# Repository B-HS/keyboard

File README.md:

# split-65

좌(30키)·우(35키) = **65키 분리형(split) 핫스왑 기계식 키보드 케이스**.
JSCAD(`@jscad/modeling`)로 파라메트릭 모델링하고, three.js 실시간 뷰어로 보며 설계하고, **FDM(A1 mini)용 3D STL**과 CNC/레이저컷용 **2D DXF** 두 경로로 export한다. **현재 제작 경로는 FDM 3D 프린트**(나사·인서트 외 전부 출력) — 아크릴 DXF 경로는 병행 보존.

> **monorepo (v0.0.1~).** React + TypeScript 뷰어(`src/`, FSD) 위에 프로젝트가 독립적으로 올라간다 — `65/`(split-65) · `keypad/`(split-keypad, 저손실 prototype). 뷰어는 현재 **65만 렌더**(keypad 코드·export·CI는 유지). 변경 이력은 [CHANGELOG.md](CHANGELOG.md), 재편 계획은 [docs/acknowledge/monorepo-keypad-migration.md](docs/acknowledge/monorepo-keypad-migration.md).

## 구조 (FDM, 위→아래)

```
top     베젤(5.0mm) + 지지 기둥 6개(Ø4.8, 일체 프린트)
plate   보강판(1.5mm) — 스위치 클립으로 PCB와 샌드위치, 기둥 홀 Ø6.4 통과
PCB     핫스왑, 마운트홀 Ø5.4 — 기둥 캡(Ø5.8)에 안착
bottom  평판(1.5mm) + 보스 + ESP32-C3 크래들
```

- **결착 = M1 하단 진입**: 마운트 6곳/측 — M1 나사가 하판 밑에서 기둥의 열간 인서트에 체결. **상면 구멍 0**, 무틸트, 총 스택 16.6mm.
- **조립**: plate에 스위치 체결 + PCB 결합(샌드위치) → 뒤집은 top의 기둥에 삽입(plate는 전부 통과, PCB는 캡에 정지) → bottom 덮고 M1 체결.
- 케이스 좌 146.4×108.2 / 우 165.4×108.3 mm. 상세: [65/docs/fdm-m1-case.md](65/docs/fdm-m1-case.md)(개정 2차) · [docs/PROCESS.md](docs/PROCESS.md).
- 이전 **아크릴 stacked 설계**(M2 관통 볼트, 스택 18.1mm)는 이력 — [docs/acknowledge/case-construction.md](docs/acknowledge/case-construction.md).

## 준비물 (구매)

### 체결 부자재 — FDM 경로 (현행)

| 부품               | 규격          | 수량 | 비고                             |
| ------------------ | ------------- | :--: | -------------------------------- |
| **M1 나사**        | M1×4mm        |  12  | 하단 진입, 기둥 인서트에 체결    |
| **M1 열간 인서트** | OD 2.0, L 2.5 |  12  | 기둥 하단 포켓(Ø1.75)에 압입     |
| **고무발**         | 높이 3~4mm    |  8   | 하단 나사머리 은닉 + 미끄럼 방지 |

> 스위치·소켓·다이오드·스태빌·컨트롤러·키캡 등 전체 빌드 목록은 **[docs/acknowledge/bom-aliexpress.md](docs/acknowledge/bom-aliexpress.md)**. 아크릴 경로(M2 관통 볼트·인서트·접착제)는 이력 — [docs/acknowledge/case-construction.md](docs/acknowledge/case-construction.md).

### 가공·발주 (별도)

- **FDM**(현행): `bun run export:65-fdm` → `65/export-out/fdm/*.stl` 측당 3장(top/plate/bottom)을 A1 mini로 출력. 1/5 검증 모형은 `export:65-fdm-mini`.
- **PCB**: KiCad(`65/pcb/{left,right}`) → JLCPCB 발주 파일 `65/pcb/order/jlcpcb-{left,right}.zip` (핫스왑 풋프린트, 사양 [65/docs/pcb-build.md](65/docs/pcb-build.md)).
- **CNC**(cast 아크릴, 병행 보존): `bun run export:65` → `65/export-out/*.dxf` 윤곽으로 발주.

## 실행

```bash
bun install
bun run dev                # three.js 실시간 뷰어 (localhost:5173, 65 좌+우)
bun run export:65-fdm      # 65 FDM STL 6장 → 65/export-out/fdm/ (측당 3: top/plate/bottom)
bun run export:65-fdm-mini # 1/5(SCALE=0.2) 검증 모형 → 65/export-out/fdm-mini/
bun run export:65          # 65 DXF 10장 → 65/export-out/ (아크릴 경로, 병행 보존)
bun run export:keypad      # keypad DXF 5장 → keypad/export-out/
bun run smoke:65           # 65 부품 생성·치수 검증
bun run smoke:keypad       # keypad 부품 생성·치수 검증
bun run typecheck          # tsc --noEmit
bun run build              # 뷰어 빌드
bun run format             # prettier
```

**뷰어**: 65(좌+우) 렌더. 부품 레이어 8개(상판·플레이트·PCB·하판·ESP32·볼트·스위치·키캡) 각각 표시·색·투명도 제어 + 비교 레퍼런스(Zen 65·49, 기본 off) + **웹 STL Export**(스케일 지정, 좌우 8장: top/plate/bottom/mock-pcb). 설정은 자동 저장. 드래그 회전 · 휠 확대 · 우클릭 이동.

## 문서

| 경로                                    | 내용                                  |
| --------------------------------------- | ------------------------------------- |
| `docs/PROCESS.md`                       | monorepo 현재 상태 단일 출처          |
| `65/docs/fdm-m1-case.md`                | FDM 케이스 설계 정본(개정 2차 = 현행) |
| `65/docs/pcb-build.md`                  | PCB 설계·JLCPCB 발주 사양             |
| `keypad/docs/PROCESS.md`                | split-keypad 프로젝트 단일 출처       |
| `docs/acknowledge/bom-aliexpress.md`    | 전체 구매 목록                        |
| `docs/acknowledge/case-construction.md` | 아크릴 케이스 구조(이력)              |
| `docs/memory/cherry-mx-dimensions.md`   | Cherry MX 표준 치수                   |

## 원본 레이아웃 (KLE-NG)

- [Left](https://editor.keyboard-tools.xyz/#share=NrBEAYBp1SMgjLeAmZUDM7IBZsFZsA2UAXUjAWmSqTirXsiybycKZPOAG9QB3UAC4EAOhT4AvnBTUZiZLMahZLFbkWRC3PoJGiA7FLgY5oU3XORlptabZXtFUDjOu6u4WInSX12HwAHsLghvhweihhvq54pKRAA)
- [Right](https://editor.keyboard-tools.xyz/#share=NrBEAYBp1SMgjLeAmZUDM7IBZsFZsA2bAdlAF1JgBvUAD1AC5wA6fAXzgWmR6W6Q0grILyDCkOgHdmCdl1A8SVWg2ZtSnOCl47EyXcNC7RJ3IciSZc1im3mV1UBj0uDcV8ddnX499agskwoiq5OasEorFqKOHo2TPL2cULI8f7xkqDxJHDx5BQUQA)

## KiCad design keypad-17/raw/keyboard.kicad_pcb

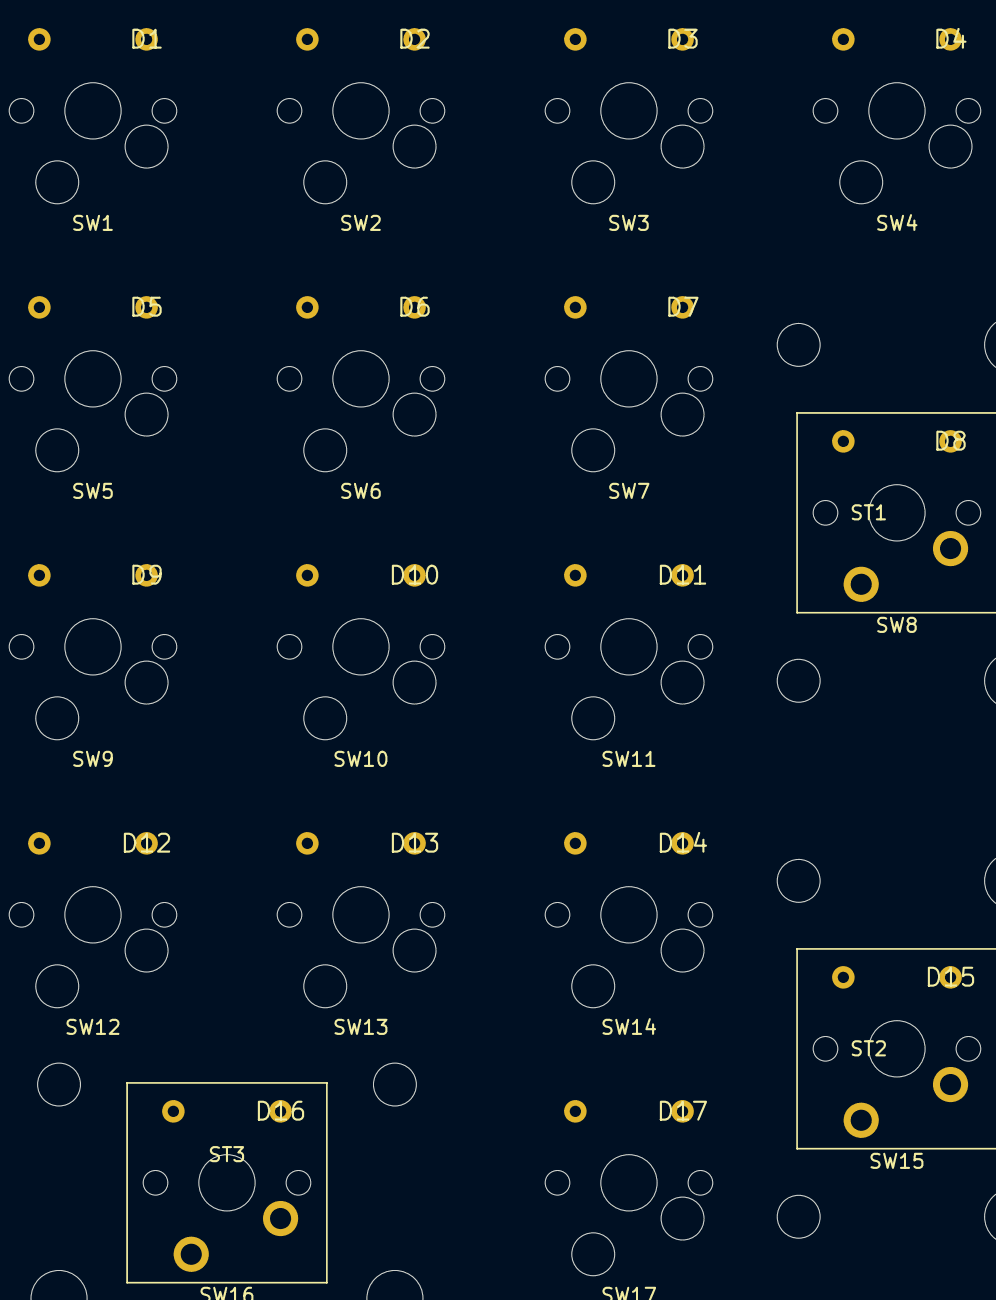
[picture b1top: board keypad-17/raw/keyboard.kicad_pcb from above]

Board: 2 copper layers, 37 parts (0 on the bottom side), 26 nets, no tracks yet.

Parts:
D1, D2, D3, D4, D5, D6, D7, D8, D9, D10, D11, D12, D13, D14, D15, D16, D17: 1N4148; D_DO-35_SOD27_P7.62mm_Horizontal
ST1, ST2, ST3: SW_stab; Stabilizer_Cherry_MX_2.00u
SW1: 0,0; SW_Cherry_MX_PCB_1.00u
SW2: 0,1; SW_Cherry_MX_PCB_1.00u
SW3: 0,2; SW_Cherry_MX_PCB_1.00u
SW4: 0,3; SW_Cherry_MX_PCB_1.00u
SW5: 1,0; SW_Cherry_MX_PCB_1.00u
SW6: 1,1; SW_Cherry_MX_PCB_1.00u
SW7: 1,2; SW_Cherry_MX_PCB_1.00u
SW8: 1,3; SW_Cherry_MX_PCB_2.00u_90deg
SW9: 2,0; SW_Cherry_MX_PCB_1.00u
SW10: 2,1; SW_Cherry_MX_PCB_1.00u
SW11: 2,2; SW_Cherry_MX_PCB_1.00u
SW12: 3,0; SW_Cherry_MX_PCB_1.00u
SW13: 3,1; SW_Cherry_MX_PCB_1.00u
SW14: 3,2; SW_Cherry_MX_PCB_1.00u
SW15: 3,3; SW_Cherry_MX_PCB_2.00u_90deg
SW16: 4,0; SW_Cherry_MX_PCB_2.00u
SW17: 4,2; SW_Cherry_MX_PCB_1.00u

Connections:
COL0: SW1.1, SW5.1, SW9.1, SW12.1, SW16.1
COL1: SW2.1, SW6.1, SW10.1, SW13.1
COL2: SW3.1, SW7.1, SW11.1, SW14.1, SW17.1
COL3: SW4.1, SW8.1, SW15.1
N_R0_C0: D1.2, SW1.2
N_R0_C1: D2.2, SW2.2
N_R0_C2: D3.2, SW3.2
N_R0_C3: D4.2, SW4.2
N_R1_C0: D5.2, SW5.2
N_R1_C1: D6.2, SW6.2
N_R1_C2: D7.2, SW7.2
N_R1_C3: D8.2, SW8.2
N_R2_C0: D9.2, SW9.2
N_R2_C1: D10.2, SW10.2
N_R2_C2: D11.2, SW11.2
N_R3_C0: D12.2, SW12.2
N_R3_C1: D13.2, SW13.2
N_R3_C2: D14.2, SW14.2
N_R3_C3: D15.2, SW15.2
N_R4_C0: D16.2, SW16.2
N_R4_C2: D17.2, SW17.2
ROW0: D1.1, D2.1, D3.1, D4.1
ROW1: D5.1, D6.1, D7.1, D8.1
ROW2: D9.1, D10.1, D11.1
ROW3: D12.1, D13.1, D14.1, D15.1
ROW4: D16.1, D17.1

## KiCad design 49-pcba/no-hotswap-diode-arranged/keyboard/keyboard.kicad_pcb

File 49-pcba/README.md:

# 나만의 작고 소듕한 키보드 만들기 프로젝트 (2) 
[Keyboard-tools](https://editor.keyboard-tools.xyz/#share=NrBEAYBp1SMgjLeAmZUDM7IBZsFZsA2bAdmwA5sBObBGOKBJRxNVhLAXUmAG9QAd1AAuBADp8AXzgJoyOS1Bz2yyFlm4FkQppKbymqptqb625rAHCxkmWoRoe-IaJT2U8uJ9WeNoTzxvHWRPfQDIQwjjCNMI82DLSGs3DzZQZ1AMLxTbFGk4bJZciXz7bPZclHFSAqytQsh9Kpq67Jiihnqk7tUi7i4gA)
- Hand wiring -> 조짐
> 연결은 다했는데 황동와이어가 너무 두껍고 49사이즈 하우징에 생각보다 들어가기가 빡셈

### 교훈 
- 객기부리지말고 KiCAD로 PCBA를 주문하자
- 케이스 두께는 최소 2.5 mm로 들어가자 (생각보다 1.5 mm도 얇음)
- 공차를 항상 1.5mm를 상정하고 출력하자 (너무 빡빡하면 사포질을 해야함)
- 표준규격을 잘 지키자 (1.5u Tabkey 이딴거 산다고 추가지출 ㅂㄷㅂㄷ)

## 주문 
- 9600 Resin + 추후 도색하던가 아니면 흰색 그대로 사용해보기 (색칠은 뭐 나중에)
- Plate는 CNC할까 생각했는데 나중에 알루로 만들 때 고려해서 그냥 CBY Resin + 3D 출력

## 결과
- 다이오드만 PCBA. 핫스왑 소켓 여유가 없을듯해서 그냥 스위치는 납땜
- 사포 필수, 자석형식으로 상판/하판 결착
- 1차에 뼈아픈 가격.. 2차도 100달러정도.. 

### 5월 말까지 완성하고 README 업데이트하기

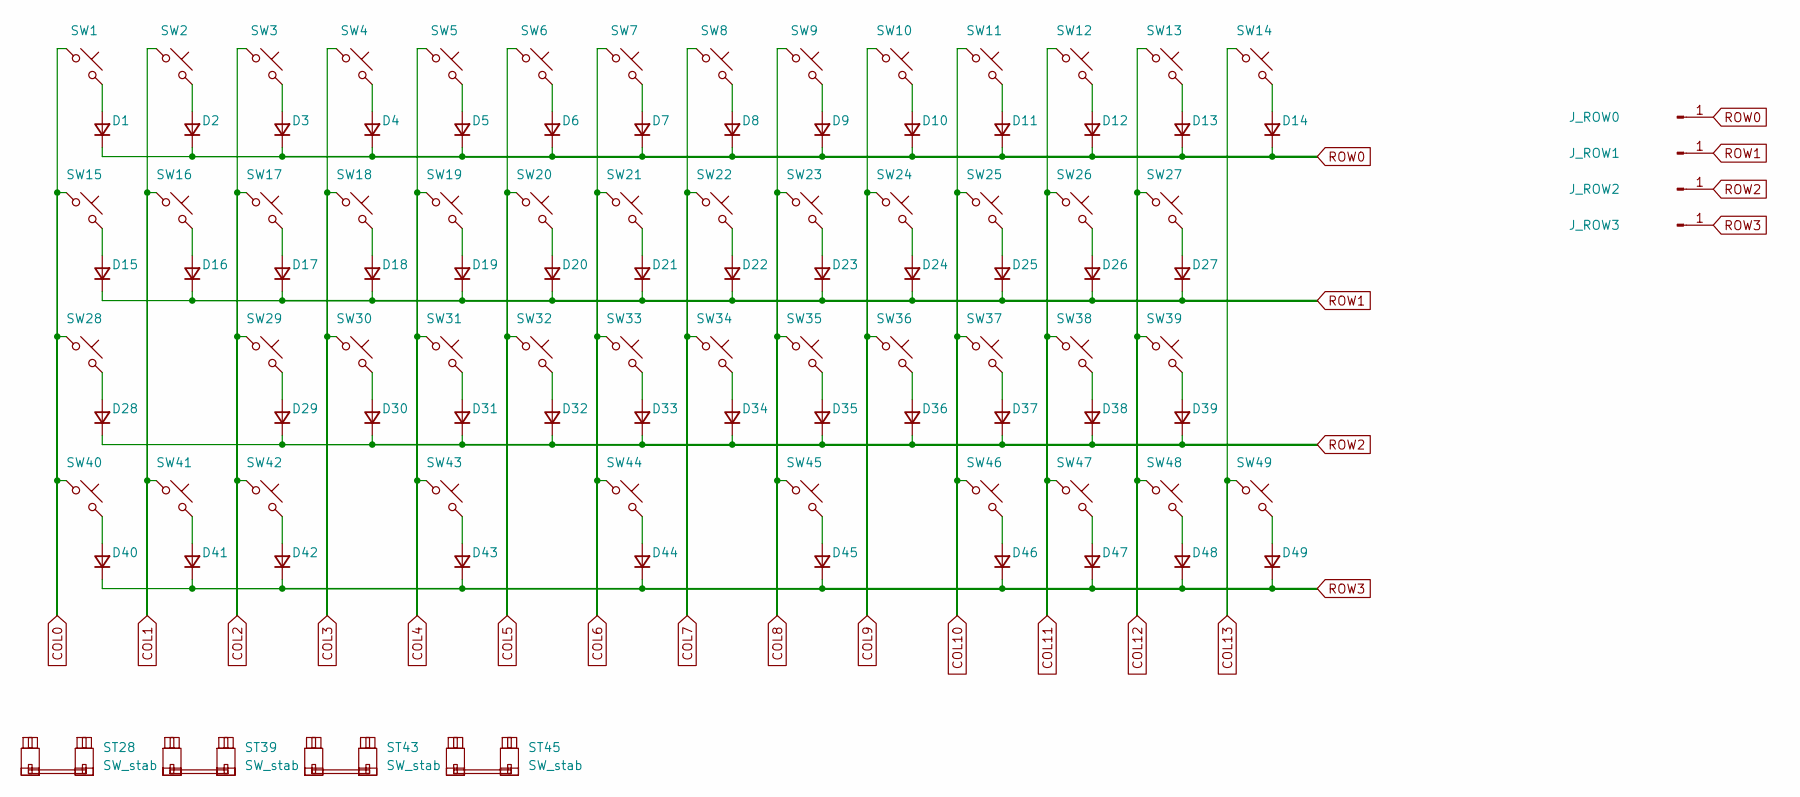
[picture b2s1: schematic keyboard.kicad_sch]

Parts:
D1, D2, D3, D4, D5, D6, D7, D8, D9, D10, D11, D12, D13, D14, D15, D16, D17, D18, D19, D20, D21, D22, D23, D24, D25, D26, D27, D28, D29, D30, D31, D32, D33, D34, D35, D36, D37, D38, D39, D40, D41, D42, D43, D44, D45, D46, D47, D48, D49: D; D_SOD-123
J_ROW0, J_ROW1, J_ROW2, J_ROW3: Conn_01x01_Pin; TestPoint_THTPad_D2.0mm_Drill1.0mm
ST28, ST39, ST43, ST45: SW_stab; Stabilizer_Cherry_MX_2.00u
SW1, SW2, SW3, SW4, SW5, SW6, SW7, SW8, SW9, SW10, SW11, SW12, SW13, SW14, SW16, SW17, SW18, SW19, SW20, SW21, SW22, SW23, SW24, SW25, SW26, SW29, SW30, SW31, SW32, SW33, SW34, SW35, SW36, SW37, SW38, SW40, SW44, SW46, SW47, SW48, SW49: SW_Push; SW_Cherry_MX_PCB_1.00u
SW15, SW27: SW_Push; SW_Cherry_MX_PCB_1.50u
SW28, SW39: SW_Push; SW_Cherry_MX_PCB_2.00u
SW41, SW42: SW_Push; SW_Cherry_MX_PCB_1.25u
SW43, SW45: SW_Push; SW_Cherry_MX_PCB_2.75u

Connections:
COL0: SW1.1, SW15.1, SW28.1, SW40.1
COL1: SW2.1, SW16.1, SW41.1
COL2: SW3.1, SW17.1, SW29.1, SW42.1
COL3: SW4.1, SW18.1, SW30.1
COL4: SW5.1, SW19.1, SW31.1, SW43.1
COL5: SW6.1, SW20.1, SW32.1
COL6: SW7.1, SW21.1, SW33.1, SW44.1
COL7: SW8.1, SW22.1, SW34.1
COL8: SW9.1, SW23.1, SW35.1, SW45.1
COL9: SW10.1, SW24.1, SW36.1
COL10: SW11.1, SW25.1, SW37.1, SW46.1
COL11: SW12.1, SW26.1, SW38.1, SW47.1
COL12: SW13.1, SW27.1, SW39.1, SW48.1
COL13: SW14.1, SW49.1
unnamed: D1.2 (A), SW1.2
unnamed: D2.2 (A), SW2.2
unnamed: D3.2 (A), SW3.2
unnamed: D4.2 (A), SW4.2
unnamed: D5.2 (A), SW5.2
unnamed: D6.2 (A), SW6.2
unnamed: D7.2 (A), SW7.2
unnamed: D8.2 (A), SW8.2
unnamed: D9.2 (A), SW9.2
unnamed: D10.2 (A), SW10.2
unnamed: D11.2 (A), SW11.2
unnamed: D12.2 (A), SW12.2
unnamed: D13.2 (A), SW13.2
unnamed: D14.2 (A), SW14.2
unnamed: D15.2 (A), SW15.2
unnamed: D16.2 (A), SW16.2
unnamed: D17.2 (A), SW17.2
unnamed: D18.2 (A), SW18.2
unnamed: D19.2 (A), SW19.2
unnamed: D20.2 (A), SW20.2
unnamed: D21.2 (A), SW21.2
unnamed: D22.2 (A), SW22.2
unnamed: D23.2 (A), SW23.2
unnamed: D24.2 (A), SW24.2
unnamed: D25.2 (A), SW25.2
unnamed: D26.2 (A), SW26.2
unnamed: D27.2 (A), SW27.2
unnamed: D28.2 (A), SW28.2
unnamed: D29.2 (A), SW29.2
unnamed: D30.2 (A), SW30.2
unnamed: D31.2 (A), SW31.2
unnamed: D32.2 (A), SW32.2
unnamed: D33.2 (A), SW33.2
unnamed: D34.2 (A), SW34.2
unnamed: D35.2 (A), SW35.2
unnamed: D36.2 (A), SW36.2
unnamed: D37.2 (A), SW37.2
unnamed: D38.2 (A), SW38.2
unnamed: D39.2 (A), SW39.2
unnamed: D40.2 (A), SW40.2
unnamed: D41.2 (A), SW41.2
unnamed: D42.2 (A), SW42.2
unnamed: D43.2 (A), SW43.2
unnamed: D44.2 (A), SW44.2
unnamed: D45.2 (A), SW45.2
unnamed: D46.2 (A), SW46.2
unnamed: D47.2 (A), SW47.2
unnamed: D48.2 (A), SW48.2
unnamed: D49.2 (A), SW49.2
ROW0: D1.1 (K), D2.1 (K), D3.1 (K), D4.1 (K), D5.1 (K), D6.1 (K), D7.1 (K), D8.1 (K), D9.1 (K), D10.1 (K), D11.1 (K), D12.1 (K), D13.1 (K), D14.1 (K), J_ROW0.1
ROW1: D15.1 (K), D16.1 (K), D17.1 (K), D18.1 (K), D19.1 (K), D20.1 (K), D21.1 (K), D22.1 (K), D23.1 (K), D24.1 (K), D25.1 (K), D26.1 (K), D27.1 (K), J_ROW1.1
ROW2: D28.1 (K), D29.1 (K), D30.1 (K), D31.1 (K), D32.1 (K), D33.1 (K), D34.1 (K), D35.1 (K), D36.1 (K), D37.1 (K), D38.1 (K), D39.1 (K), J_ROW2.1
ROW3: D40.1 (K), D41.1 (K), D42.1 (K), D43.1 (K), D44.1 (K), D45.1 (K), D46.1 (K), D47.1 (K), D48.1 (K), D49.1 (K), J_ROW3.1

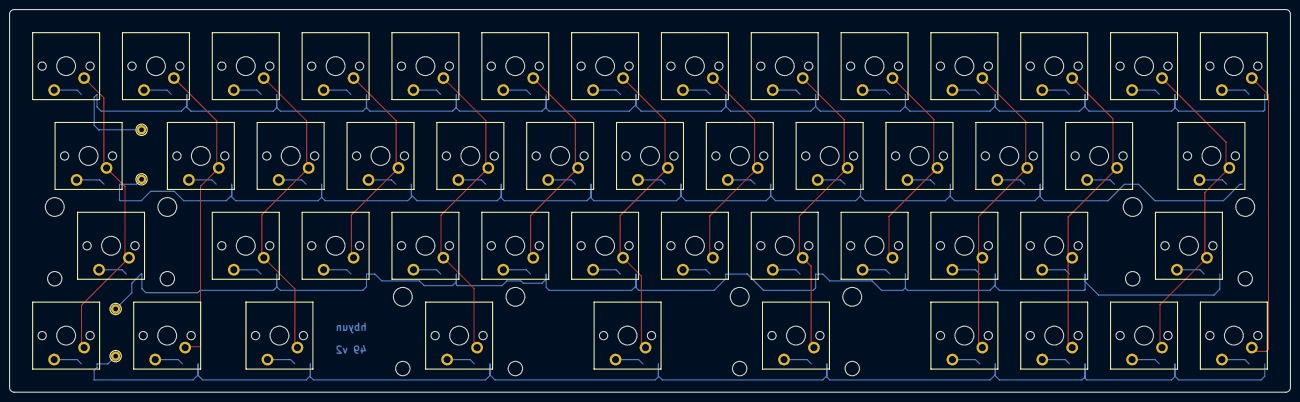
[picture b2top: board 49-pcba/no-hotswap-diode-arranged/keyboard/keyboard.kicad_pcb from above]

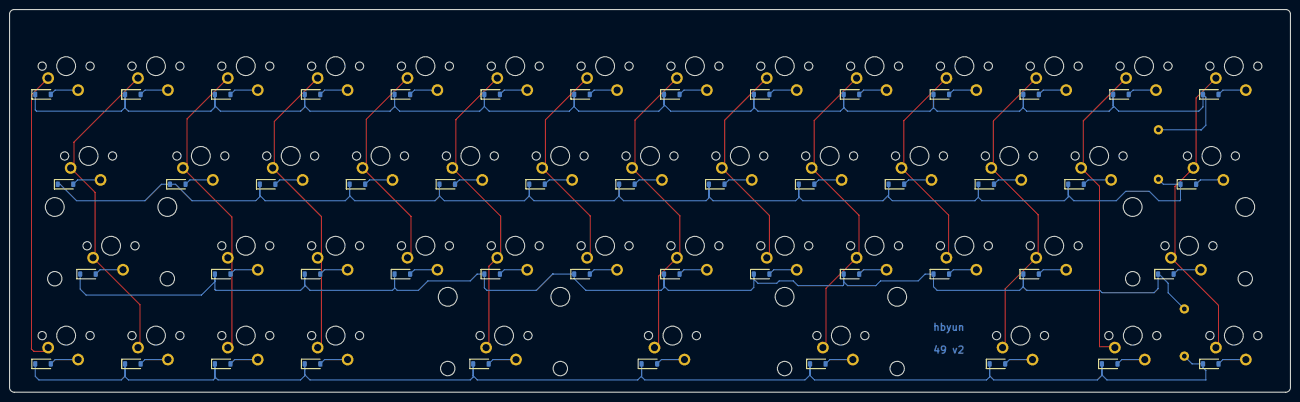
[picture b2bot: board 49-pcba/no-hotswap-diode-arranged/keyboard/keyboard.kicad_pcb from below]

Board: 2 copper layers, 271.6 x 81.1 mm, 106 parts (49 on the bottom side), 67 nets.

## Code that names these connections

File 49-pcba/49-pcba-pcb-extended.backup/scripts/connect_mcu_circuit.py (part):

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        'VDD': '+3V3', 'VDDA': '+3V3', 'VBAT': '+3V3', 'VDDIO2': '+3V3',
        'VSS': 'GND', 'VSSA': 'GND',
        'NRST': 'NRST', 'BOOT0': 'BOOT0',
        'PA0': 'COL0', 'PA1': 'COL1', 'PA2': 'COL2', 'PA3': 'COL3',
        'PA4': 'COL4', 'PA5': 'COL5', 'PA6': 'COL6', 'PA7': 'COL7',
        'PA8': 'COL13',
        'PA11': 'USB_DM', 'PA12': 'USB_DP',
        'PA13': 'SWDIO', 'PA14': 'SWCLK',
        'PB0': 'ROW0', 'PB1': 'ROW1', 'PB2': 'ROW2', 'PB10': 'ROW3',
        'PB3': 'COL8', 'PB4': 'COL9', 'PB5': 'COL10',
        'PB6': 'COL11', 'PB7': 'COL12',
        # 나머지 PA9, PA10, PA15, PB8, PB9, PB11~15, PC13~15, PF0/1 → 라벨 X (LED 등 미래)
    },
}
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
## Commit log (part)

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2026-03-09 Add files
2026-03-09 Add keyboard layout link to layout.md
2026-03-09 Expand README with project phases and tasks
    Added detailed project phases for custom keyboard development including PCB design, housing design, firmware, and prototyping.
2026-04-03 Fix layout and add prebuilded files
2026-04-17 Update files
2026-04-17 Remove ignorefile
2026-04-19 Update files with prerenderer
2026-04-19 WIP : divide backside case
2026-04-19 Union the plate into case
2026-04-20 Finishing 3d files
2026-04-20 Add publishing and
2026-04-20 Fix clip z value for stabilizer
2026-04-20 Update context
2026-04-20 Adjust cutsize
2026-04-20 fix: fix minor issues
2026-04-21 Update files to tranform two files from 3
2026-04-21 Add fixment
2026-04-21 Update shpaes
2026-04-25 Create documentation for keyboard layout model
    Add a new model documentation with JSON structure for keyboard layout.
2026-05-03 Create v2 version of own keyboard
2026-05-03 Adjust heights for pcb/plate and overall size for cases
2026-05-03 Adjust stl logic
2026-05-03 Finalize V2 before create PCB
2026-05-09 Cutoff usb-c hole and add esp32-s3
2026-05-09 Update PCB with routing
2026-05-09 Clean up files with completed PCB rendering
2026-05-09 Finalize v2 with pcb, case files
2026-05-09 Clean up model preview with generated PCB from kicad
2026-05-09 Update README.md"
2026-05-09 Clean up keycap and rendering view
2026-05-22 Add initial firmawre
